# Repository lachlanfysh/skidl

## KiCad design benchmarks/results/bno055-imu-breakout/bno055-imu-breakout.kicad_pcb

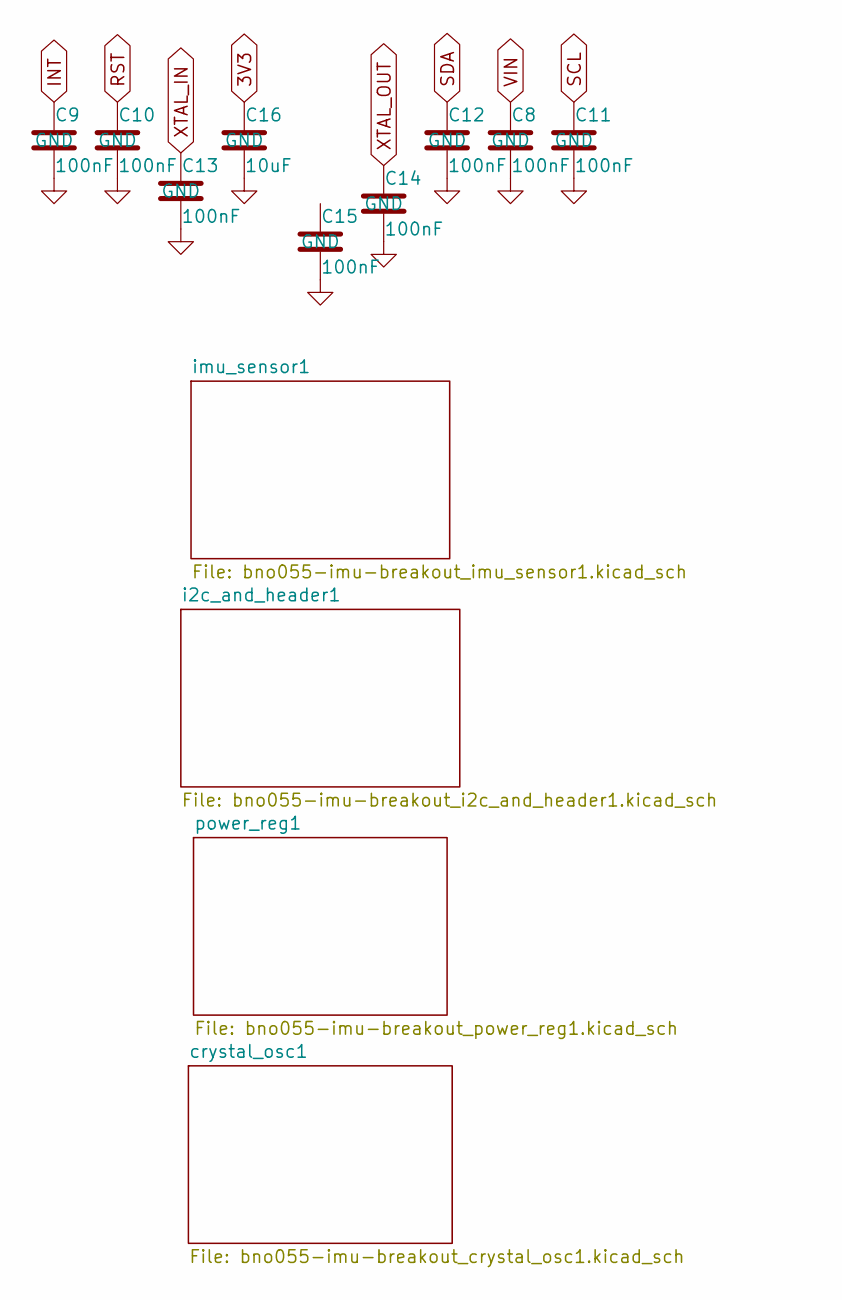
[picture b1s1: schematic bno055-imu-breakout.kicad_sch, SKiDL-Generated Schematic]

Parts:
C8, C9, C10, C11, C12, C13, C14, C15: 100nF; C_0603_1608Metric
C16: 10uF; C_0805_2012Metric

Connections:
3V3: C16.1; also elsewhere on the board
GND: C8.2, C9.2, C10.2, C11.2, C12.2, C13.2, C14.2, C15.2, C16.2; also elsewhere on the board
INT: C9.1; also elsewhere on the board
RST: C10.1; also elsewhere on the board
SCL: C11.1; also elsewhere on the board
SDA: C12.1; also elsewhere on the board
VIN: C8.1; also elsewhere on the board
XTAL_IN: C13.1; also elsewhere on the board
XTAL_OUT: C14.1; also elsewhere on the board

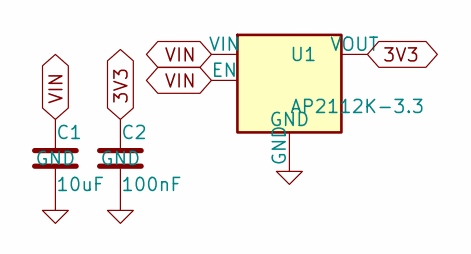
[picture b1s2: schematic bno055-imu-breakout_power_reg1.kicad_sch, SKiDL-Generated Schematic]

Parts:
C1: 10uF; C_0805_2012Metric
C2: 100nF; C_0603_1608Metric
U1: AP2112K-3.3; SOT-23-5

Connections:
3V3: C2.1, U1.5 (VOUT); also elsewhere on the board
GND: C1.2, C2.2, U1.2 (GND); also elsewhere on the board
VIN: C1.1, U1.1 (VIN), U1.3 (EN); also elsewhere on the board

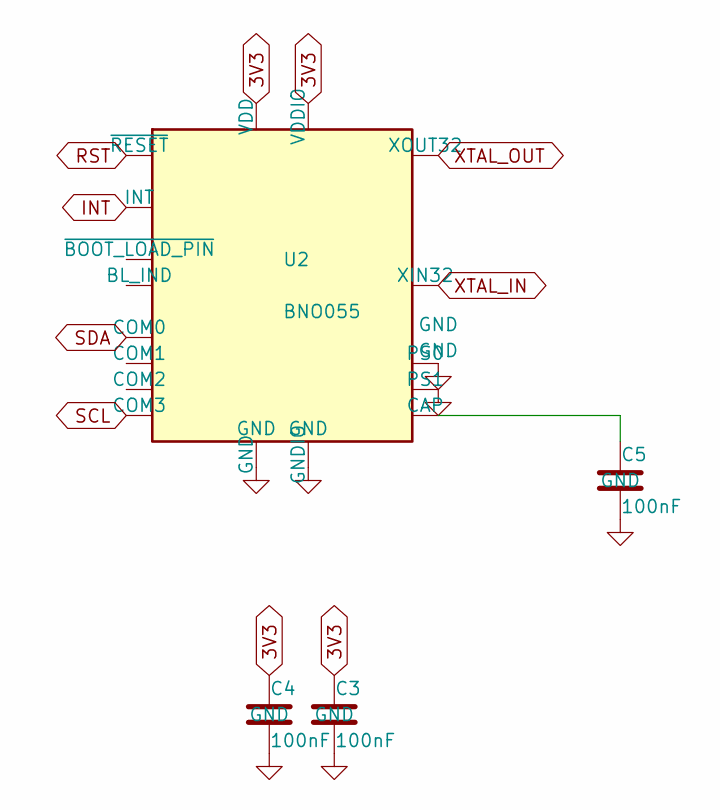
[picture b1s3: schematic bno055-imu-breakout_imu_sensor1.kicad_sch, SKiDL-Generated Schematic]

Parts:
C3, C4, C5: 100nF; C_0603_1608Metric
U2: BNO055; LGA-28_5.2x3.8mm_P0.5mm

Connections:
3V3: C3.1, C4.1, U2.3 (VDD), U2.28 (VDDIO); also elsewhere on the board
GND: C3.2, C4.2, C5.2, U2.2 (GND), U2.5 (PS1), U2.6 (PS0), U2.25 (GNDIO); also elsewhere on the board
INT: U2.14 (INT); also elsewhere on the board
unnamed: C5.1, U2.9 (CAP)
RST: U2.11 (~RESET); also elsewhere on the board
SCL: U2.17 (COM3); also elsewhere on the board
SDA: U2.20 (COM0); also elsewhere on the board
XTAL_IN: U2.27 (XIN32); also elsewhere on the board
XTAL_OUT: U2.26 (XOUT32); also elsewhere on the board

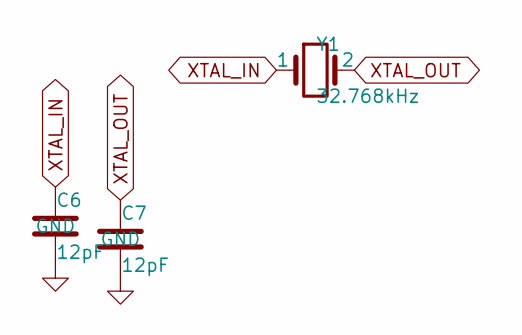
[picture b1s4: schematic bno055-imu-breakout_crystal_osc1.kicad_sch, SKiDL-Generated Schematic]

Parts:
C6, C7: 12pF; C_0402_1005Metric
Y1: 32.768kHz; Crystal_SMD_3215-2Pin_3.2x1.5mm

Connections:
GND: C6.2, C7.2; also elsewhere on the board
XTAL_IN: C6.1, Y1.1; also elsewhere on the board
XTAL_OUT: C7.1, Y1.2; also elsewhere on the board

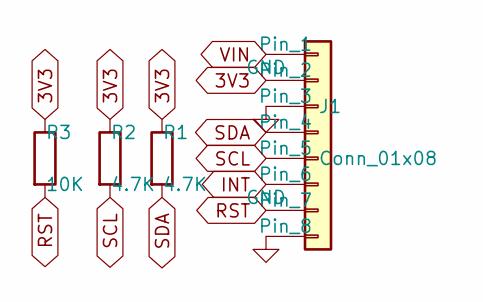
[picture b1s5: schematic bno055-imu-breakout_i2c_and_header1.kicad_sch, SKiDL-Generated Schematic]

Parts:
J1: Conn_01x08; PinHeader_1x08_P2.54mm_Vertical
R1, R2: 4.7K; R_0603_1608Metric
R3: 10K; R_0603_1608Metric

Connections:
3V3: J1.2, R1.1, R2.1, R3.1; also elsewhere on the board
GND: J1.3, J1.8; also elsewhere on the board
INT: J1.6; also elsewhere on the board
RST: J1.7, R3.2; also elsewhere on the board
SCL: J1.5, R2.2; also elsewhere on the board
SDA: J1.4, R1.2; also elsewhere on the board
VIN: J1.1; also elsewhere on the board

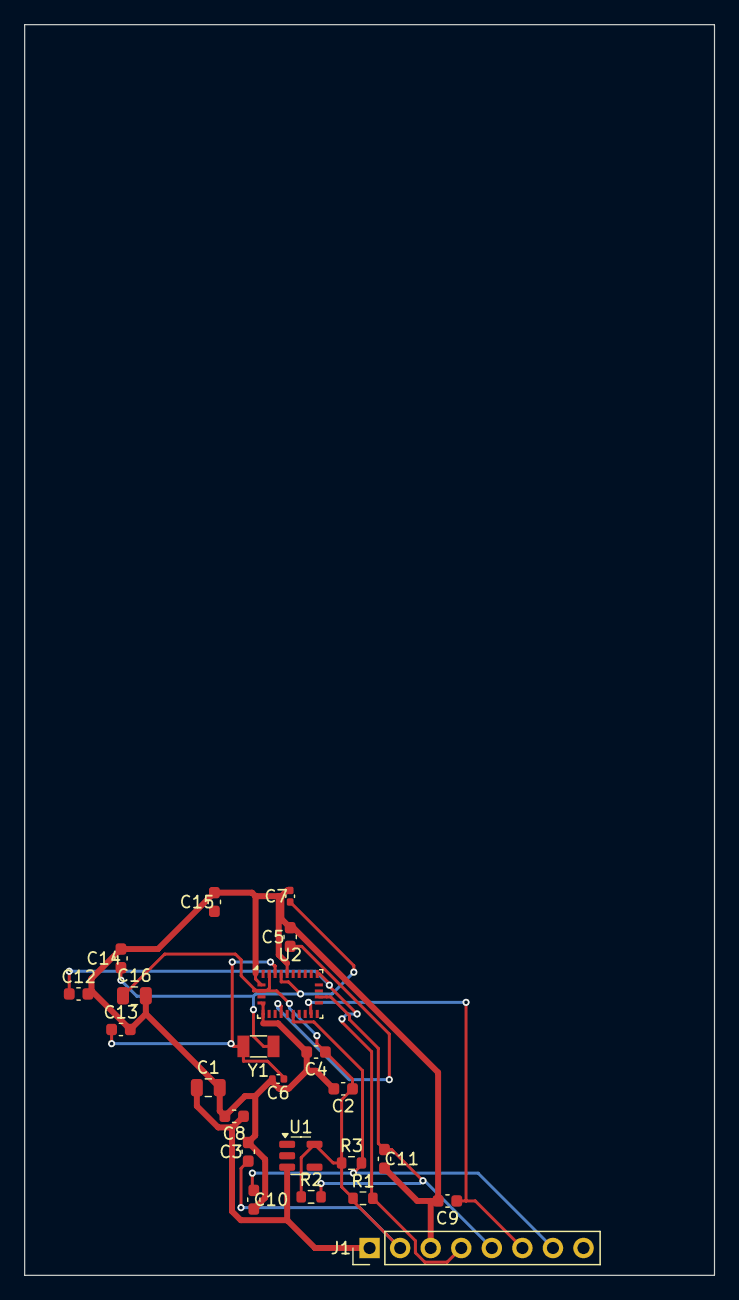
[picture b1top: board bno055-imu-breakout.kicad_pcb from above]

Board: 2 copper layers, 57.3 x 103.9 mm, 23 parts (0 on the bottom side), 10 nets.

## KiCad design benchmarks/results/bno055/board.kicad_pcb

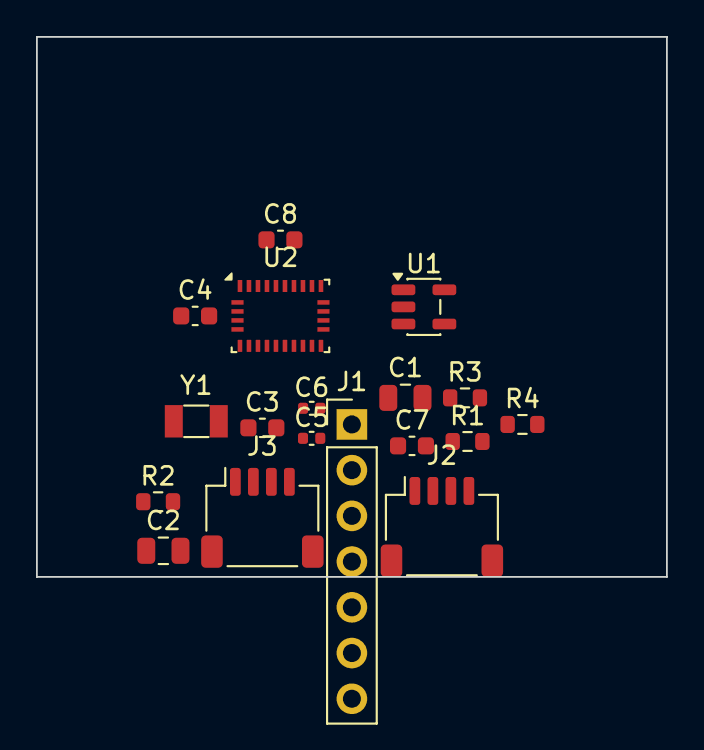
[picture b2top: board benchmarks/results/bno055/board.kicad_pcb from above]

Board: 2 copper layers, 35.0 x 30.0 mm, 18 parts (0 on the bottom side), 10 nets, no tracks yet.

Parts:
C1, C2: 10uF; C_0805_2012Metric
C3, C4, C7, C8: 100nF; C_0603_1608Metric
C5, C6: 12pF; C_0402_1005Metric
J1: Header; PinHeader_1x07_P2.54mm_Vertical
J2, J3: STEMMA_QT; JST_SH_SM04B-SRSS-TB_1x04-1MP_P1.00mm_Horizontal
R1, R2: 4.7K; R_0603_1608Metric
R3, R4: 10K; R_0603_1608Metric
U1: AP2112K-3.3; SOT-23-5
U2: BNO055; LGA-28_5.2x3.8mm_P0.5mm
Y1: 32.768kHz; Crystal_SMD_3215-2Pin_3.2x1.5mm

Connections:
+3V3: C2.1, C3.1, C7.1, C8.1, J1.2, J2.2, J3.2, R1.1, R2.1, R3.1, R4.1, U1.5, U2.3, U2.4, U2.28
BNO_CAP: C4.1, U2.9
GND: C1.2, C2.2, C3.2, C4.2, C5.2, C6.2, C7.2, C8.2, J1.3, J2.1, J3.1, U1.2, U2.2, U2.5, U2.6, U2.17, U2.18, U2.25
INT: J1.6, R4.2, U2.14
unnamed: U2.27, Y1.1
unnamed: U2.26, Y1.2
SCL: J1.5, J2.4, J3.4, R2.2, U2.19
SDA: J1.4, J2.3, J3.3, R1.2, U2.20
VIN: C1.1, J1.1, U1.1, U1.3
nRESET: J1.7, R3.2, U2.11

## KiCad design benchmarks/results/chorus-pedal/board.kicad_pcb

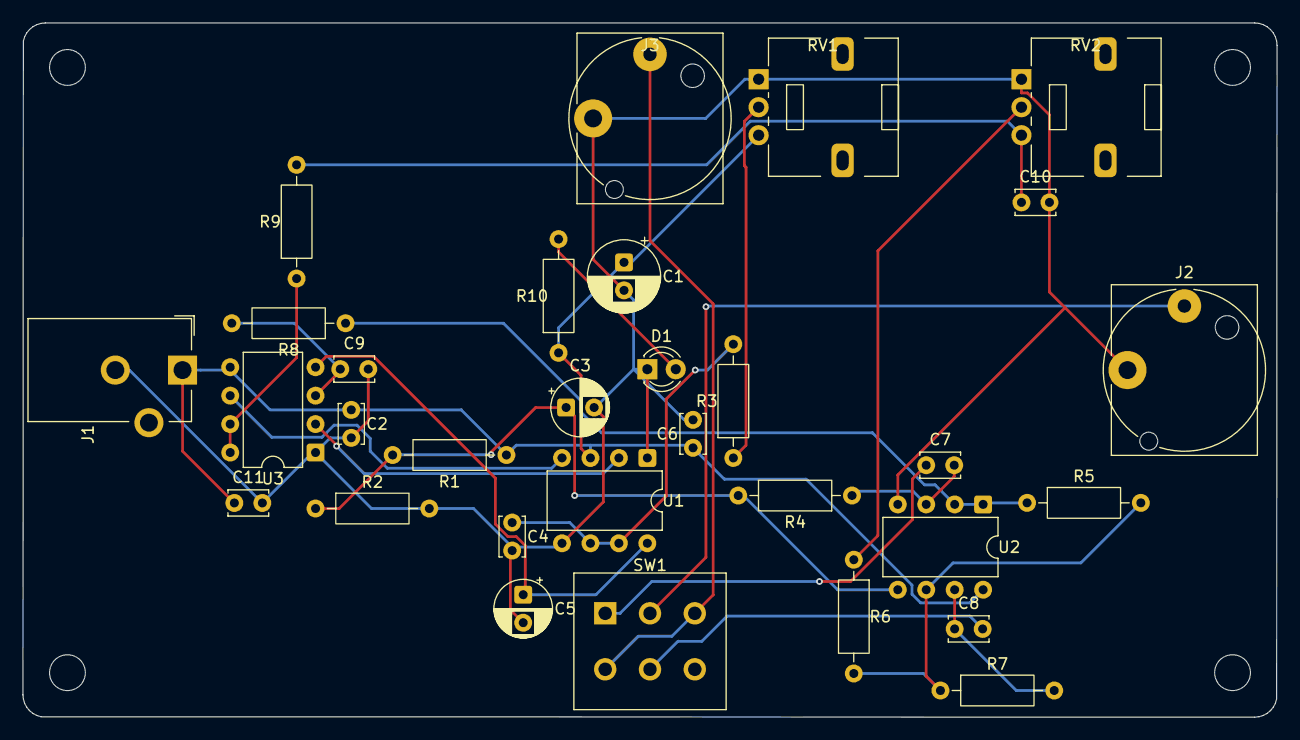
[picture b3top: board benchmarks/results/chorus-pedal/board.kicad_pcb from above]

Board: 2 copper layers, 112.0 x 62.0 mm, 35 parts (0 on the bottom side), 21 nets.

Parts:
C1: 100uF; CP_Radial_D6.3mm_P2.50mm
C2, C6, C7, C8, C11: 100nF; C_Disc_D3.4mm_W2.1mm_P2.50mm
C3: 47uF; CP_Radial_D5.0mm_P2.50mm
C4: 10nF; C_Disc_D3.4mm_W2.1mm_P2.50mm
C5: 10uF; CP_Radial_D5.0mm_P2.50mm
C9, C10: 5.6nF; C_Disc_D3.4mm_W2.1mm_P2.50mm
D1: LED; LED_D3.0mm
H1, H2, H3, H4: MountingHole; MountingHole_3.2mm_M3
J1: Barrel_Jack; BarrelJack_CUI_PJ-102AH_Horizontal
J2, J3: AudioJack2; Jack_6.35mm_Neutrik_NJ2FD-V_Vertical
R1, R2: 47K; R_Axial_DIN0207_L6.3mm_D2.5mm_P10.16mm_Horizontal
R3: 10K; R_Axial_DIN0207_L6.3mm_D2.5mm_P10.16mm_Horizontal
R4: 1M; R_Axial_DIN0207_L6.3mm_D2.5mm_P10.16mm_Horizontal
R5, R6, R7, R8, R9: 22K; R_Axial_DIN0207_L6.3mm_D2.5mm_P10.16mm_Horizontal
R10: 4.7K; R_Axial_DIN0207_L6.3mm_D2.5mm_P10.16mm_Horizontal
RV1, RV2: 50K; Potentiometer_Alps_RK09L_Single_Vertical
SW1: SW_DPDT_x2; SW_PUSH_E-Switch_FS5700DP_DPDT
U1: MN3101; DIP-8_W7.62mm
U2: TL072; DIP-8_W7.62mm
U3: MN3007; DIP-8_W7.62mm

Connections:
AUDIO_IN: J2.T, SW1.2
AUDIO_OUT: J3.T, SW1.3, SW1.4
BBD_IN: C9.1, R8.2, U3.3
BBD_OUT: C10.1, R9.2, RV2.3
BBD_OUT2_PRE: R9.1, U3.7, U3.8
BUF_OUT: R5.1, R8.1, U2.1, U2.2
CIRCUIT_IN: C7.1, SW1.1
CIRCUIT_OUT: C8.2, SW1.5
CP1: U1.2, U3.2
CP2: U1.4, U3.6
DEPTH_WIP: R6.1, RV2.2
GND: C1.2, C2.2, C3.2, C4.2, C5.2, C6.2, C9.2, C10.2, C11.2, D1.1, J1.2, J2.S, J3.S, R2.2, RV1.1, RV2.1, U1.1, U1.5, U2.4, U3.1
IN_NODE: C7.2, R4.1, U2.3
MIXER_OUT: C8.1, R7.2, U2.7
MIX_NODE: R5.2, R6.2, R7.1, U2.6
unnamed: R3.1, RV1.2
unnamed: D1.2, R10.2
OSC_NODE: C4.1, R3.2, U1.6, U1.7
VBAT: C1.1, C2.1, C6.1, C11.1, J1.1, R1.1, R10.1, RV1.3, U1.3, U2.8, U3.5
VGG: C5.1, U1.8, U3.4
VREF: C3.1, R1.2, R2.1, R4.2, U2.5

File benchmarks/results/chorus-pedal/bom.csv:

Comment,Designator,Footprint,LCSC Part Number
Barrel_Jack,J1,Connector_BarrelJack:BarrelJack_CUI_PJ-102AH_Horizontal,
100uF,C1,Capacitor_THT:CP_Radial_D6.3mm_P2.50mm,
100nF,C2,Capacitor_THT:C_Disc_D3.4mm_W2.1mm_P2.50mm,
47K,R1,Resistor_THT:R_Axial_DIN0207_L6.3mm_D2.5mm_P10.16mm_Horizontal,
47K,R2,Resistor_THT:R_Axial_DIN0207_L6.3mm_D2.5mm_P10.16mm_Horizontal,
47uF,C3,Capacitor_THT:CP_Radial_D5.0mm_P2.50mm,
MN3101,U1,Package_DIP:DIP-8_W7.62mm,
50K,RV1,Potentiometer_THT:Potentiometer_Alps_RK09L_Single_Vertical,
10K,R3,Resistor_THT:R_Axial_DIN0207_L6.3mm_D2.5mm_P10.16mm_Horizontal,
10nF,C4,Capacitor_THT:C_Disc_D3.4mm_W2.1mm_P2.50mm,
10uF,C5,Capacitor_THT:CP_Radial_D5.0mm_P2.50mm,
100nF,C6,Capacitor_THT:C_Disc_D3.4mm_W2.1mm_P2.50mm,
50K,RV2,Potentiometer_THT:Potentiometer_Alps_RK09L_Single_Vertical,
TL072,U2,Package_DIP:DIP-8_W7.62mm,
1M,R4,Resistor_THT:R_Axial_DIN0207_L6.3mm_D2.5mm_P10.16mm_Horizontal,
100nF,C7,Capacitor_THT:C_Disc_D3.4mm_W2.1mm_P2.50mm,
22K,R5,Resistor_THT:R_Axial_DIN0207_L6.3mm_D2.5mm_P10.16mm_Horizontal,
22K,R6,Resistor_THT:R_Axial_DIN0207_L6.3mm_D2.5mm_P10.16mm_Horizontal,
22K,R7,Resistor_THT:R_Axial_DIN0207_L6.3mm_D2.5mm_P10.16mm_Horizontal,
100nF,C8,Capacitor_THT:C_Disc_D3.4mm_W2.1mm_P2.50mm,
MN3007,U3,Package_DIP:DIP-8_W7.62mm,
22K,R8,Resistor_THT:R_Axial_DIN0207_L6.3mm_D2.5mm_P10.16mm_Horizontal,
5.6nF,C9,Capacitor_THT:C_Disc_D3.4mm_W2.1mm_P2.50mm,
22K,R9,Resistor_THT:R_Axial_DIN0207_L6.3mm_D2.5mm_P10.16mm_Horizontal,
5.6nF,C10,Capacitor_THT:C_Disc_D3.4mm_W2.1mm_P2.50mm,
100nF,C11,Capacitor_THT:C_Disc_D3.4mm_W2.1mm_P2.50mm,
AudioJack2,J2,Connector_Audio:Jack_6.35mm_Neutrik_NJ2FD-V_Vertical,
AudioJack2,J3,Connector_Audio:Jack_6.35mm_Neutrik_NJ2FD-V_Vertical,
SW_DPDT_x2,SW1,Button_Switch_THT:SW_PUSH_E-Switch_FS5700DP_DPDT,
4.7K,R10,Resistor_THT:R_Axial_DIN0207_L6.3mm_D2.5mm_P10.16mm_Horizontal,
LED,D1,LED_THT:LED_D3.0mm,
MountingHole,H1,MountingHole:MountingHole_3.2mm_M3,
MountingHole,H2,MountingHole:MountingHole_3.2mm_M3,
MountingHole,H3,MountingHole:MountingHole_3.2mm_M3,
MountingHole,H4,MountingHole:MountingHole_3.2mm_M3,

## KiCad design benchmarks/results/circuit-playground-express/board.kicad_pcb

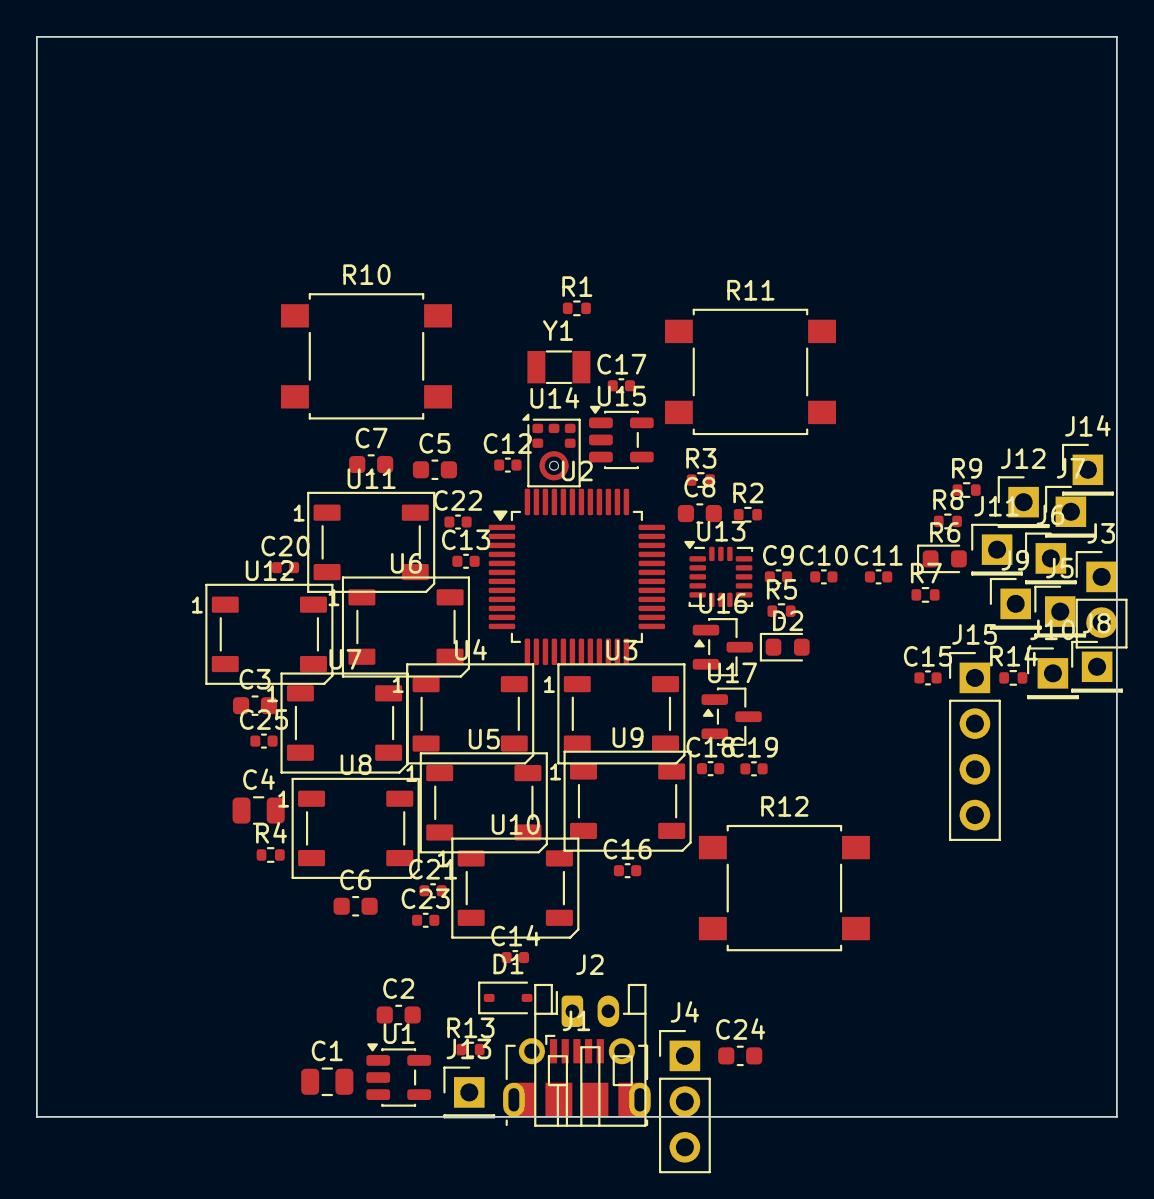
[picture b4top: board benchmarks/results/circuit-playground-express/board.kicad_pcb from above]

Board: 2 copper layers, 60.0 x 60.0 mm, 74 parts (0 on the bottom side), 29 nets, no tracks yet.

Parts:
C1, C4: 10uF; C_0805_2012Metric
C2, C3, C5, C6, C7, C8, C24: 100nF; C_0603_1608Metric
C9, C10: 12pF; C_0402_1005Metric
C11, C12, C13, C14, C15, C16, C17, C18, C19, C20, C21, C22, C23, C25: 100nF; C_0402_1005Metric
D1: MBR0520; D_SOD-323
D2: IR_LED; LED_0603_1608Metric
J1: USB_Micro-B; USB_Micro-B_Molex-105017-0001
J2: BATT; JST_PH_S2B-PH-K_1x02_P2.00mm_Horizontal
J3: SPEAKER; PinHeader_1x02_P2.54mm_Vertical
J4: SLIDE_SW; PinHeader_1x03_P2.54mm_Vertical
J5: PAD_A0; PinHeader_1x01_P2.54mm_Vertical
J6: PAD_A1; PinHeader_1x01_P2.54mm_Vertical
J7: PAD_A2; PinHeader_1x01_P2.54mm_Vertical
J8: PAD_A3; PinHeader_1x01_P2.54mm_Vertical
J9: PAD_A4; PinHeader_1x01_P2.54mm_Vertical
J10: PAD_A5; PinHeader_1x01_P2.54mm_Vertical
J11: PAD_A6; PinHeader_1x01_P2.54mm_Vertical
J12: PAD_A7; PinHeader_1x01_P2.54mm_Vertical
J13: PAD_3V3; PinHeader_1x01_P2.54mm_Vertical
J14: PAD_GND; PinHeader_1x01_P2.54mm_Vertical
J15: SWD; PinHeader_1x04_P2.54mm_Vertical
R1, R7, R9, R13, R14: 10K; R_0402_1005Metric
R2, R3: 4.7K; R_0402_1005Metric
R4: 100R; R_0402_1005Metric
R5: 1K; R_0402_1005Metric
R6: PHOTOTRANS; LED_0603_1608Metric
R8: 10K_NTC; R_0402_1005Metric
R10: SW_A; SW_SPST_B3S-1000
R11: SW_B; SW_SPST_B3S-1000
R12: SW_RST; SW_SPST_B3S-1000
U1: AP2112K-3.3; SOT-23-5
U2: ATSAMD21G18A; TQFP-48_7x7mm_P0.5mm
U3: WS2812B_0; LED_WS2812B_PLCC4_5.0x5.0mm_P3.2mm
U4: WS2812B_1; LED_WS2812B_PLCC4_5.0x5.0mm_P3.2mm
U5: WS2812B_2; LED_WS2812B_PLCC4_5.0x5.0mm_P3.2mm
U6: WS2812B_3; LED_WS2812B_PLCC4_5.0x5.0mm_P3.2mm
U7: WS2812B_4; LED_WS2812B_PLCC4_5.0x5.0mm_P3.2mm
U8: WS2812B_5; LED_WS2812B_PLCC4_5.0x5.0mm_P3.2mm
U9: WS2812B_6; LED_WS2812B_PLCC4_5.0x5.0mm_P3.2mm
U10: WS2812B_7; LED_WS2812B_PLCC4_5.0x5.0mm_P3.2mm
U11: WS2812B_8; LED_WS2812B_PLCC4_5.0x5.0mm_P3.2mm
U12: WS2812B_9; LED_WS2812B_PLCC4_5.0x5.0mm_P3.2mm
U13: LIS3DH; Analog_LGA-16_3.25x3mm_P0.5mm_LayoutBorder3x5y
U14: SPH0645LM4H; Knowles_SPH0645LM4H-6_3.5x2.65mm
U15: PAM8301; SOT-23-5
U16: MMBT3904; SOT-23
U17: TSOP38238; SOT-23
Y1: 32.768kHz; Crystal_SMD_3215-2Pin_3.2x1.5mm

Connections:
+3V3: C3.1, C4.1, C6.1, C7.1, C8.1, C12.1, C13.1, C14.1, C15.1, C16.1, C17.1, C18.1, C19.1, C20.1, C21.1, C22.1, C23.1, C24.1, C25.1, J4.3, J13.1, J15.1, R1.1, R2.1, R3.1, R4.1, R6.1, R8.1, R13.1, R14.1, U1.5, U2.6, U2.17, U2.36, U2.44, U3.1, U4.1, U5.1, U6.1, U7.1, U8.1, U9.1, U10.1, U11.1, U12.1, U13.1, U13.8, U13.14, U14.6, U15.1, U15.5, U17.3
GND: C1.2, C2.2, C3.2, C4.2, C5.2, C6.2, C7.2, C8.2, C9.2, C10.2, C11.2, C12.2, C13.2, C14.2, C15.2, C16.2, C17.2, C18.2, C19.2, C20.2, C21.2, C22.2, C23.2, C24.2, C25.2, J1.5, J1.6, J2.2, J3.2, J4.1, J14.1, J15.2, R7.2, R9.2, R10.2, R11.2, R12.2, U1.2, U2.5, U2.18, U2.35, U2.42, U3.3, U4.3, U5.3, U6.3, U7.3, U8.3, U9.3, U10.3, U11.3, U12.3, U13.5, U13.7, U13.10, U13.12, U14.2, U14.5, U15.3, U16.2, U17.2
IR_RX: U2.12, U17.1
IR_TX: R5.1, U2.10
LIGHT: R6.2, R7.1, U2.7
MIC_OUT: U2.8, U14.3
unnamed: C9.1, U2.1, Y1.1
unnamed: C10.1, U2.2, Y1.2
unnamed: C11.1, R1.2, U2.40
unnamed: R5.2, U16.1
unnamed: D2.2, U16.3
unnamed: D2.1, R4.2
NEOPIX: U2.11, U3.4
NEO_0: U3.2, U4.4
NEO_1: U4.2, U5.4
NEO_2: U5.2, U6.4
NEO_3: U6.2, U7.4
NEO_4: U7.2, U8.4
NEO_5: U8.2, U9.4
NEO_6: U9.2, U10.4
NEO_7: U10.2, U11.4
NEO_8: U11.2, U12.4
SCL: R3.2, U2.32, U13.4
SDA: R2.2, U2.31, U13.6
SPEAKER: U2.3, U15.2
SPK_OUT: J3.1, U15.4
TEMP: R8.2, R9.1, U2.14
VBUS: C1.1, C2.1, D1.1, D1.2, J1.1, J2.1, U1.1, U1.3
VDDCORE: C5.1, U2.43

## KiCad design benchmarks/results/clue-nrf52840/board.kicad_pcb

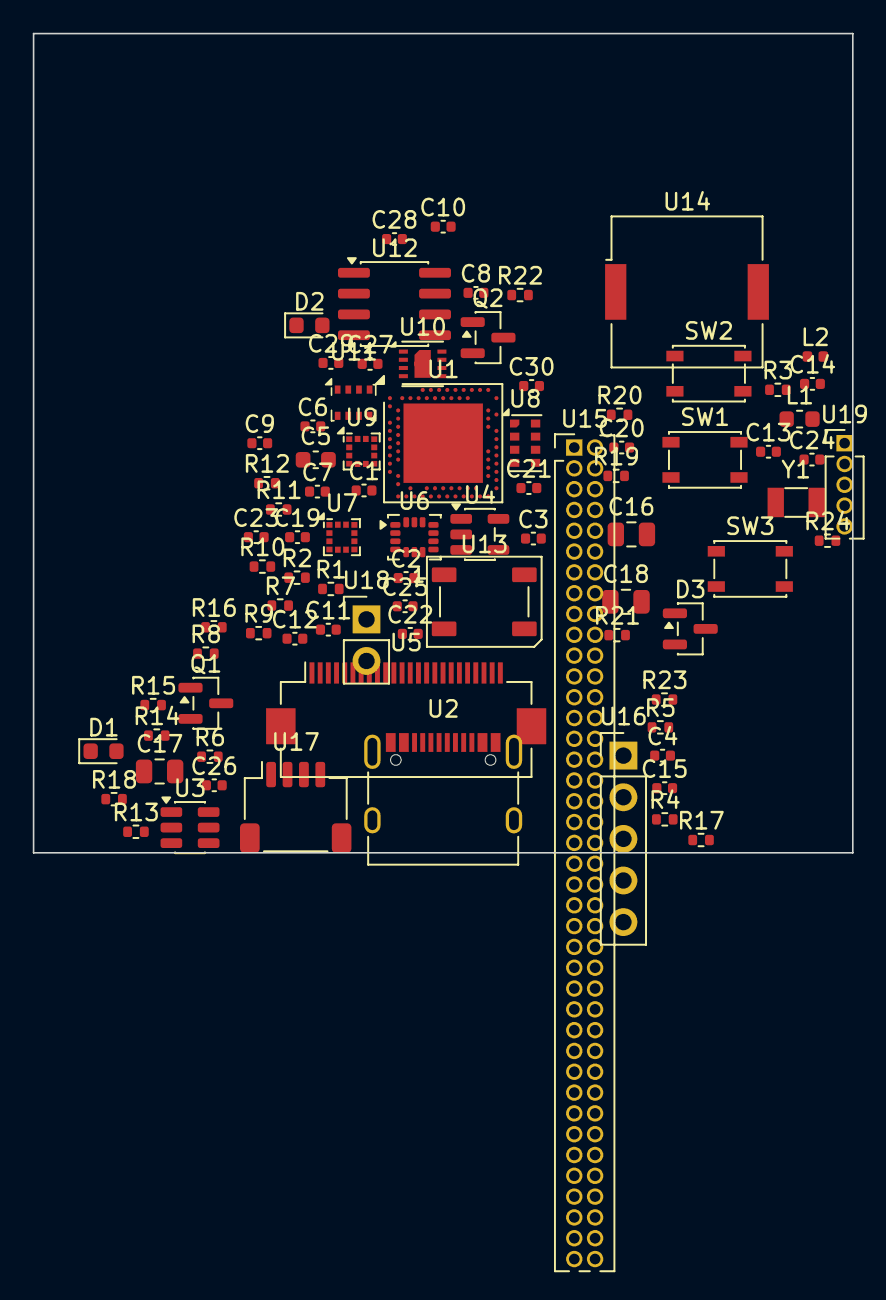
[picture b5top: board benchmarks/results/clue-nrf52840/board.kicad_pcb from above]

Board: 2 copper layers, 50.0 x 50.0 mm, 84 parts (0 on the bottom side), 34 nets, no tracks yet.

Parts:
C1, C2, C3, C4, C6, C7, C8, C9, C10, C11, C12, C19, C20, C21, C22, C23, C24, C25, C26, C27, C28, C29, C30: 100nF; C_0402_1005Metric
C5: 4.7uF; C_0603_1608Metric
C13, C14: 12pF; C_0402_1005Metric
C15: 0.8pF; C_0402_1005Metric
C16, C17, C18: 10uF; C_0805_2012Metric
D1, D2: White; LED_0603_1608Metric
D3: MBR0520; SOT-23
L1: 10uH; L_0603_1608Metric
L2: 3.3nH; L_0402_1005Metric
Q1, Q2: BSS138; SOT-23
R1, R2: 4.7K; R_0402_1005Metric
R3, R8, R9, R10, R11, R12, R13, R14, R15, R16, R17, R18, R20: 10K; R_0402_1005Metric
R4, R5: 5.1K; R_0402_1005Metric
R6, R7: 1M; R_0402_1005Metric
R19: 68; R_0402_1005Metric
R21: 470; R_0402_1005Metric
R22: 1K; R_0402_1005Metric
R23, R24: 100; R_0402_1005Metric
SW1, SW2, SW3: Button; SW_SPST_PTS810
U1: nRF52840; Nordic_AQFN-73-1EP_7x7mm_P0.5mm
U2: USB_C_Receptacle; USB_C_Receptacle_XKB_U262-16XN-4BVC11
U3: TPD2E001; SOT-23-6
U4: AP2112K-3.3; SOT-23-5
U5: TFT_FFC_24P; Hirose_FH12-24S-0.5SH_1x24-1MP_P0.50mm_Horizontal
U6: LSM6DS33; LGA-14_3x2.5mm_P0.5mm_LayoutBorder3x4y
U7: LIS3MDL; LGA-12_2x2mm_P0.5mm
U8: APDS-9960; AMS_OLGA-8_2x3.1mm_P0.8mm
U9: MP34DT01; LGA-12_2x2mm_P0.5mm
U10: SHT30; Sensirion_DFN-8-1EP_2.5x2.5mm_P0.5mm_EP1.1x1.7mm
U11: BMP280; Bosch_LGA-8_2x2.5mm_P0.65mm_ClockwisePinNumbering
U12: GD25Q16C; SOIC-8_3.9x4.9mm_P1.27mm
U13: WS2812B; LED_WS2812B_PLCC4_5.0x5.0mm_P3.2mm
U14: Buzzer; Buzzer_Murata_PKMCS0909E
U15: Edge_Connector; PinHeader_2x40_P1.27mm_Vertical
U16: BigPads; PinHeader_1x05_P2.54mm_Vertical
U17: STEMMA_QT; JST_SH_SM04B-SRSS-TB_1x04-1MP_P1.00mm_Horizontal
U18: Battery_JST; PinHeader_1x02_P2.54mm_Vertical
U19: SWD_Header; PinHeader_1x05_P1.27mm_Vertical
Y1: 32.768kHz; Crystal_SMD_3215-2Pin_3.2x1.5mm

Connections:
+3V3: C1.1, C2.1, C3.1, C4.1, C5.1, C18.1, C19.1, C20.1, C21.1, C22.1, C24.1, C25.1, C26.1, C27.1, C28.1, C29.1, C30.1, L1.2, R1.1, R2.1, R3.1, R19.1, U4.5, U5.5, U5.6, U5.23, U6.5, U6.8, U6.12, U7.4, U7.5, U7.11, U8.2, U9.1, U10.5, U10.6, U11.2, U11.6, U11.8, U12.3, U12.7, U12.8, U13.1, U14.1, U15.1, U15.2, U16.4, U17.2, U19.1
ANT_FEED: C15.1, L2.2
FLASH_CS: U1.P23, U12.1
GND: C1.2, C2.2, C3.2, C4.2, C5.2, C6.2, C7.2, C8.2, C9.2, C10.2, C11.2, C12.2, C13.2, C14.2, C15.2, C16.2, C17.2, C18.2, C19.2, C20.2, C21.2, C22.2, C23.2, C24.2, C25.2, C26.2, C27.2, C28.2, C29.2, C30.2, D1.1, D2.1, R4.2, R5.2, R6.2, R7.2, R8.2, R9.2, R10.2, R11.2, R12.2, R13.2, R14.2, R15.2, R16.2, R17.2, R18.2, R20.2, SW1.2, SW2.2, SW3.2, U1.EP, U3.2, U4.2, U5.1, U5.7, U5.24, U6.1, U6.6, U6.7, U7.2, U7.8, U7.10, U7.12, U8.5, U8.7, U9.2, U9.3, U9.6, U9.7, U9.8, U9.9, U9.10, U9.11, U9.12, U10.2, U10.7, U10.8, U10.9, U11.1, U11.5, U11.7, U12.4, U13.3, U15.3, U15.4, U16.5, U17.1, U17.MP, U18.2, U19.5
unnamed: L1.1, U1.P2
unnamed: C13.1, Y1.1
unnamed: C14.1, Y1.2
unnamed: R9.1, U5.8
unnamed: R10.1, U5.9
unnamed: R11.1, U5.10
unnamed: R12.1, U5.11
unnamed: R13.1, U5.12
unnamed: R14.1, U5.13
unnamed: R15.1, U5.14
unnamed: R16.1, U5.15
unnamed: R17.1, U5.18
unnamed: R18.1, U5.19
unnamed: C23.1, U7.3
unnamed: R19.2, U8.6
unnamed: R20.1, U8.3
unnamed: D1.2, R23.2
unnamed: D2.2, R24.2
unnamed: U15.5, U16.1
unnamed: U15.6, U16.2
unnamed: U15.7, U16.3
unnamed: D3.2, U18.1
NEOPIXEL_DATA: R21.1, R21.2, U13.4
SCL: R2.2, U6.3, U6.13, U7.1, U8.8, U10.4, U11.4, U17.4
SDA: R1.2, U6.2, U6.14, U7.9, U8.1, U10.1, U11.3, U17.3
SPI_CLK: U5.22, U12.6
SPI_MISO: U12.2, U15.8
SPI_MOSI: U5.21, U12.5
TFT_BL_SINK: U5.2, U5.3, U5.4
VBUS: C16.1, C17.1, D3.1, U3.5, U4.1, U4.3

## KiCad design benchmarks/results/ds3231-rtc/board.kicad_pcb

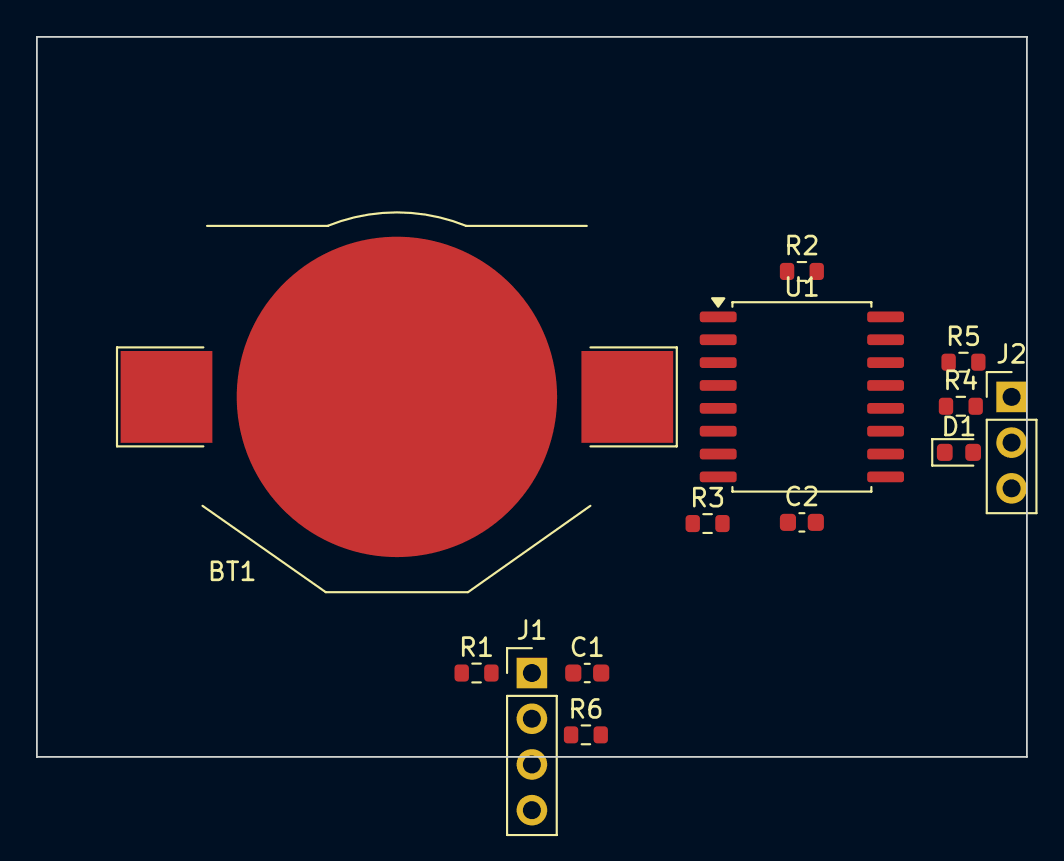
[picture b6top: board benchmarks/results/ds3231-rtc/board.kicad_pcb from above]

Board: 2 copper layers, 55.0 x 40.0 mm, 13 parts (0 on the bottom side), 9 nets, no tracks yet.

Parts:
BT1: CR2032; BatteryHolder_Keystone_3002_1x2032
C1, C2: 100nF; C_0603_1608Metric
D1: Green; LED_0603_1608Metric
J1: I2C; PinHeader_1x04_P2.54mm_Vertical
J2: AUX_OUT; PinHeader_1x03_P2.54mm_Vertical
R1, R2, R3, R4: 4.7K; R_0603_1608Metric
R5: 10K; R_0603_1608Metric
R6: 1K; R_0603_1608Metric
U1: DS3231M; SOIC-16W_7.5x10.3mm_P1.27mm

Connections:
GND: BT1.2, C1.2, C2.2, D1.2, J1.2, J2.3, U1.5, U1.6, U1.7, U1.8, U1.9, U1.10, U1.11, U1.12, U1.13
unnamed: D1.1, R6.2
OUT_32K: J2.2, R4.2, U1.1
RST_N: R5.2, U1.4
SCL: J1.4, R2.2, U1.16
SDA: J1.3, R1.2, U1.15
SQW_INT: J2.1, R3.2, U1.3
VBAT: BT1.1, C2.1, U1.14
VCC: C1.1, J1.1, R1.1, R2.1, R3.1, R4.1, R5.1, R6.1, U1.2

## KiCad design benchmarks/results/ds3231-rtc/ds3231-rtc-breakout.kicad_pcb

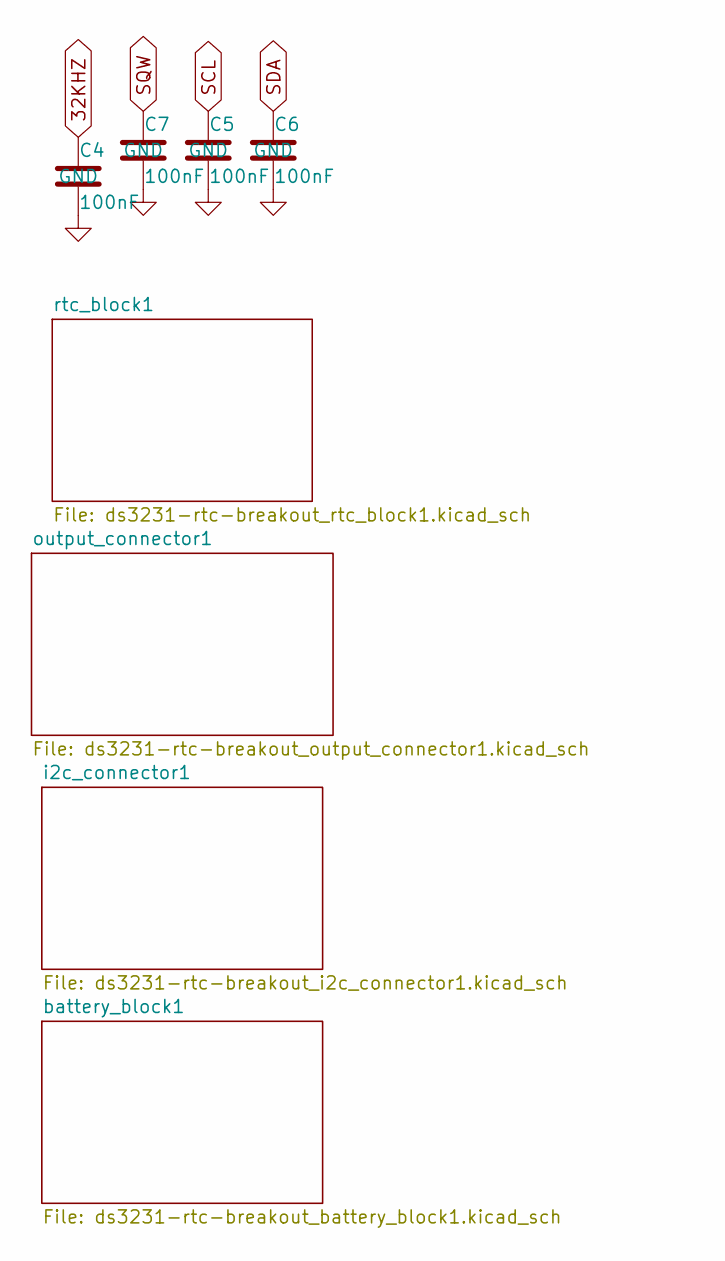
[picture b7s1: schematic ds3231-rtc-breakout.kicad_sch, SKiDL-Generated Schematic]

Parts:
C4, C5, C6, C7: 100nF; C_0603_1608Metric

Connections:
32KHZ: C4.1; also elsewhere on the board
GND: C4.2, C5.2, C6.2, C7.2; also elsewhere on the board
SCL: C5.1; also elsewhere on the board
SDA: C6.1; also elsewhere on the board
SQW: C7.1; also elsewhere on the board

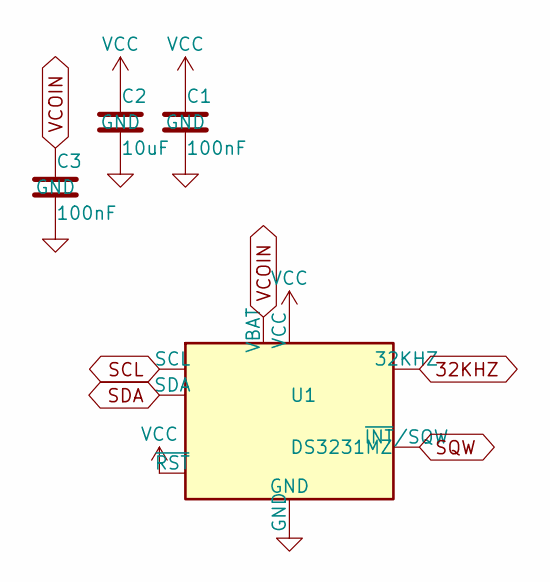
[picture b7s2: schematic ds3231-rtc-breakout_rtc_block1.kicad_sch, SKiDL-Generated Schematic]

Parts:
C1, C3: 100nF; C_0603_1608Metric
C2: 10uF; C_0805_2012Metric
U1: DS3231MZ; SOIC-8_3.9x4.9mm_P1.27mm

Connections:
32KHZ: U1.1 (32KHZ); also elsewhere on the board
GND: C1.2, C2.2, C3.2, U1.5 (GND); also elsewhere on the board
SCL: U1.8 (SCL); also elsewhere on the board
SDA: U1.7 (SDA); also elsewhere on the board
SQW: U1.3 (~INT/SQW); also elsewhere on the board
VCC: C1.1, C2.1, U1.2 (VCC), U1.4 (~RST); also elsewhere on the board
VCOIN: C3.1, U1.6 (VBAT); also elsewhere on the board

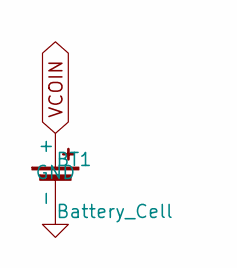
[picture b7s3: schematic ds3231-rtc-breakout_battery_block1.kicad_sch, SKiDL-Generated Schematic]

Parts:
BT1: Battery_Cell; BatteryHolder_Keystone_3034_1x20mm

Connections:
GND: BT1.2 (-); also elsewhere on the board
VCOIN: BT1.1 (+); also elsewhere on the board

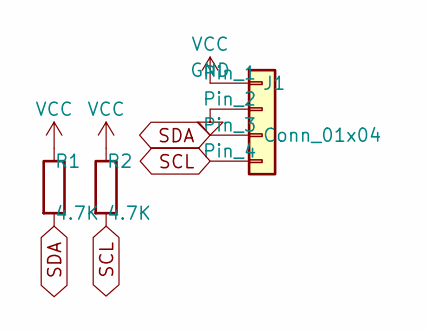
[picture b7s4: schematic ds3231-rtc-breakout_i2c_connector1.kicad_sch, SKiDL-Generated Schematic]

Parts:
J1: Conn_01x04; PinHeader_1x04_P2.54mm_Vertical
R1, R2: 4.7K; R_0603_1608Metric

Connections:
GND: J1.2; also elsewhere on the board
SCL: J1.4, R2.2; also elsewhere on the board
SDA: J1.3, R1.2; also elsewhere on the board
VCC: J1.1, R1.1, R2.1; also elsewhere on the board

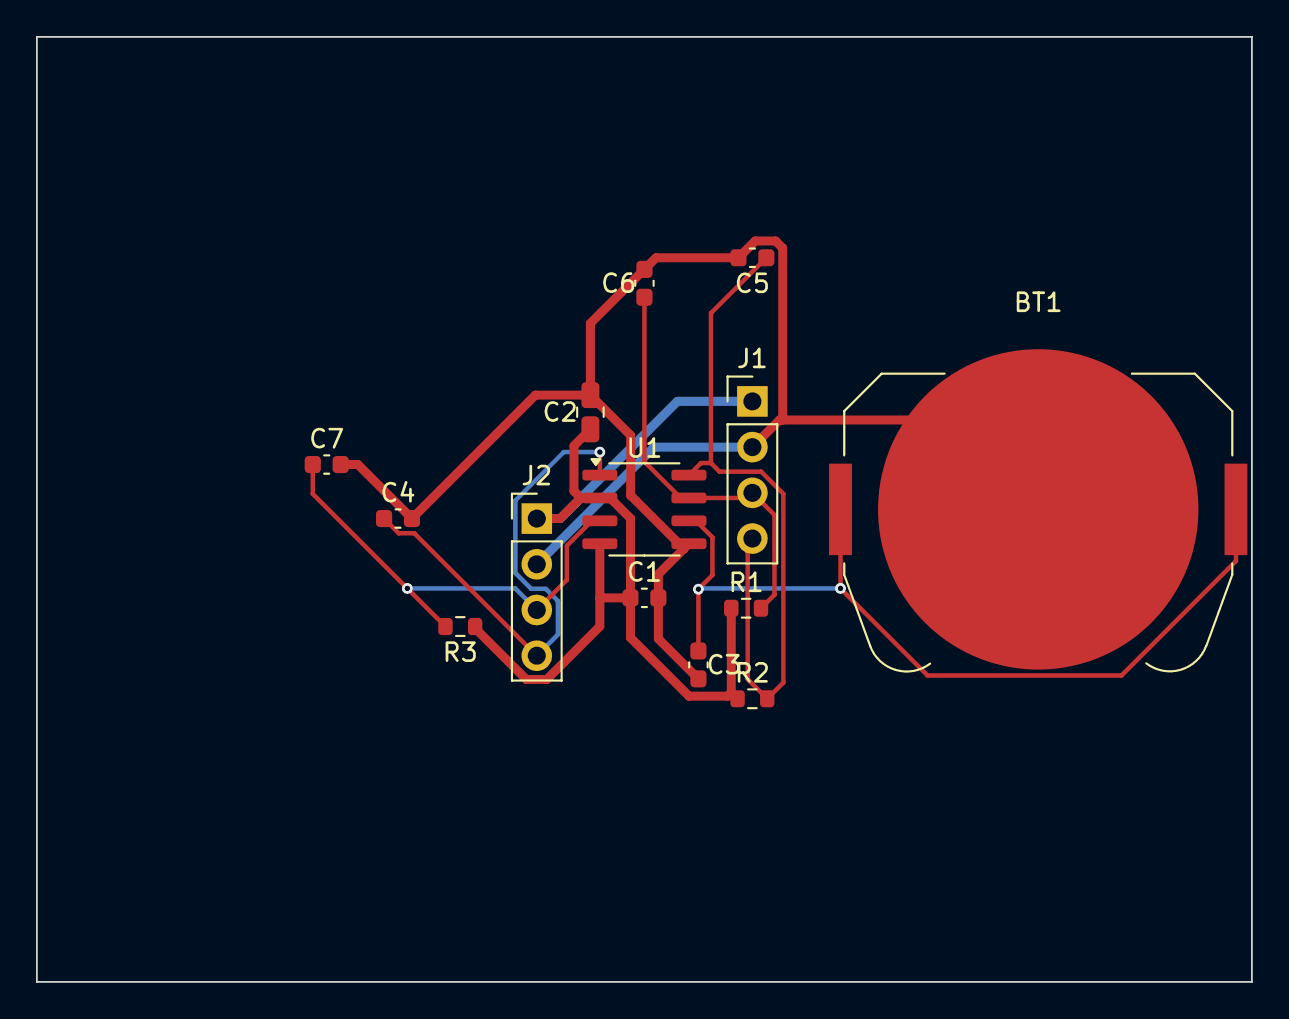
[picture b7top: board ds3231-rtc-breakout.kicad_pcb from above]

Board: 2 copper layers, 67.5 x 52.5 mm, 14 parts (0 on the bottom side), 7 nets.

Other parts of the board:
J2: Conn_01x04; PinHeader_1x04_P2.54mm_Vertical
R3: 10K; R_0603_1608Metric

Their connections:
32KHZ: J2.4; also elsewhere on the board
GND: J2.2; also elsewhere on the board
SQW: J2.3, R3.2; also elsewhere on the board
VCC: J2.1, R3.1; also elsewhere on the board

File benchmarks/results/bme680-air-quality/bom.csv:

Comment,Designator,Footprint,LCSC Part Number
Conn_01x06,J1,Connector_PinHeader_2.54mm:PinHeader_1x06_P2.54mm_Vertical,
AP2112K-3.3,U1,Package_TO_SOT_SMD:SOT-23-5,
1uF,C1,Capacitor_SMD:C_0603_1608Metric,
10uF,C2,Capacitor_SMD:C_0805_2012Metric,
100nF,C3,Capacitor_SMD:C_0603_1608Metric,
TXB0104D,U2,Package_SO:SOIC-14_3.9x8.7mm_P1.27mm,
100nF,C4,Capacitor_SMD:C_0603_1608Metric,
100nF,C5,Capacitor_SMD:C_0603_1608Metric,
BME680,U3,Package_LGA:Bosch_LGA-8_3x3mm_P0.8mm_ClockwisePinNumbering,
100nF,C6,Capacitor_SMD:C_0402_1005Metric,
100nF,C7,Capacitor_SMD:C_0402_1005Metric,
4.7K,R1,Resistor_SMD:R_0603_1608Metric,
4.7K,R2,Resistor_SMD:R_0603_1608Metric,
10K,R3,Resistor_SMD:R_0603_1608Metric,
10uF,C8,Capacitor_SMD:C_0805_2012Metric,
